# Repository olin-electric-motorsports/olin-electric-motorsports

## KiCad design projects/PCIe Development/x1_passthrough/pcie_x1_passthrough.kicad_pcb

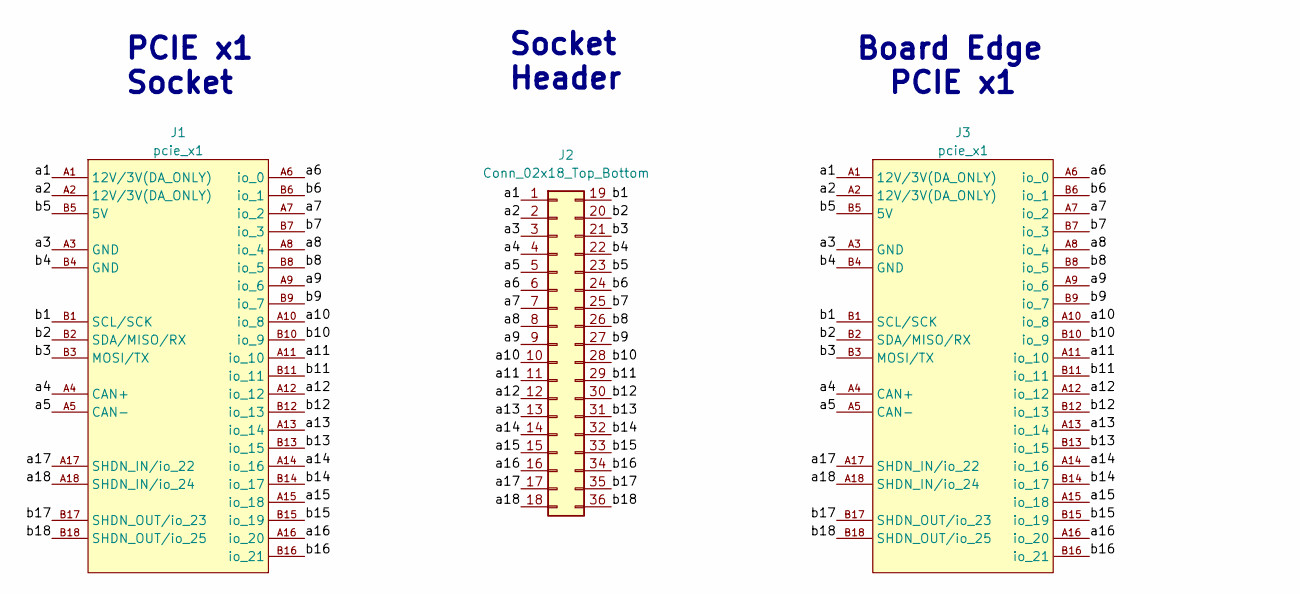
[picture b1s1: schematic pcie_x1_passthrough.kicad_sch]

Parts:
J1: pcie_x1; te_pcie_x1_connector
J2: Conn_02x18_Top_Bottom; PinSocket_2x18_P2.54mm_Vertical
J3: pcie_x1

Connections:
/a1: J1.A1 (12V/3V(DA_ONLY)), J2.1, J3.A1 (12V/3V(DA_ONLY))
/a2: J1.A2 (12V/3V(DA_ONLY)), J2.2, J3.A2 (12V/3V(DA_ONLY))
/a3: J1.A3 (GND), J2.3, J3.A3 (GND)
/a4: J1.A4 (CAN+), J2.4, J3.A4 (CAN+)
/a5: J1.A5 (CAN-), J2.5, J3.A5 (CAN-)
/a6: J1.A6 (io_0), J2.6, J3.A6 (io_0)
/a7: J1.A7 (io_2), J2.7, J3.A7 (io_2)
/a8: J1.A8 (io_4), J2.8, J3.A8 (io_4)
/a9: J1.A9 (io_6), J2.9, J3.A9 (io_6)
/a10: J1.A10 (io_8), J2.10, J3.A10 (io_8)
/a11: J1.A11 (io_10), J2.11, J3.A11 (io_10)
/a12: J1.A12 (io_12), J2.12, J3.A12 (io_12)
/a13: J1.A13 (io_14), J2.13, J3.A13 (io_14)
/a14: J1.A14 (io_16), J2.14, J3.A14 (io_16)
/a15: J1.A15 (io_18), J2.15, J3.A15 (io_18)
/a16: J1.A16 (io_20), J2.16, J3.A16 (io_20)
/a17: J1.A17 (SHDN_IN/io_22), J2.17, J3.A17 (SHDN_IN/io_22)
/a18: J1.A18 (SHDN_IN/io_24), J2.18, J3.A18 (SHDN_IN/io_24)
/b1: J1.B1 (SCL/SCK), J2.19, J3.B1 (SCL/SCK)
/b2: J1.B2 (SDA/MISO/RX), J2.20, J3.B2 (SDA/MISO/RX)
/b3: J1.B3 (MOSI/TX), J2.21, J3.B3 (MOSI/TX)
/b4: J1.B4 (GND), J2.22, J3.B4 (GND)
/b5: J1.B5 (5V), J2.23, J3.B5 (5V)
/b6: J1.B6 (io_1), J2.24, J3.B6 (io_1)
/b7: J1.B7 (io_3), J2.25, J3.B7 (io_3)
/b8: J1.B8 (io_5), J2.26, J3.B8 (io_5)
/b9: J1.B9 (io_7), J2.27, J3.B9 (io_7)
/b10: J1.B10 (io_9), J2.28, J3.B10 (io_9)
/b11: J1.B11 (io_11), J2.29, J3.B11 (io_11)
/b12: J1.B12 (io_13), J2.30, J3.B12 (io_13)
/b13: J1.B13 (io_15), J2.31, J3.B13 (io_15)
/b14: J1.B14 (io_17), J2.32, J3.B14 (io_17)
/b15: J1.B15 (io_19), J2.33, J3.B15 (io_19)
/b16: J1.B16 (io_21), J2.34, J3.B16 (io_21)
/b17: J1.B17 (SHDN_OUT/io_23), J2.35, J3.B17 (SHDN_OUT/io_23)
/b18: J1.B18 (SHDN_OUT/io_25), J2.36, J3.B18 (SHDN_OUT/io_25)

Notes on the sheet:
Socket Header
Board Edge PCIE x1
PCIE x1 Socket

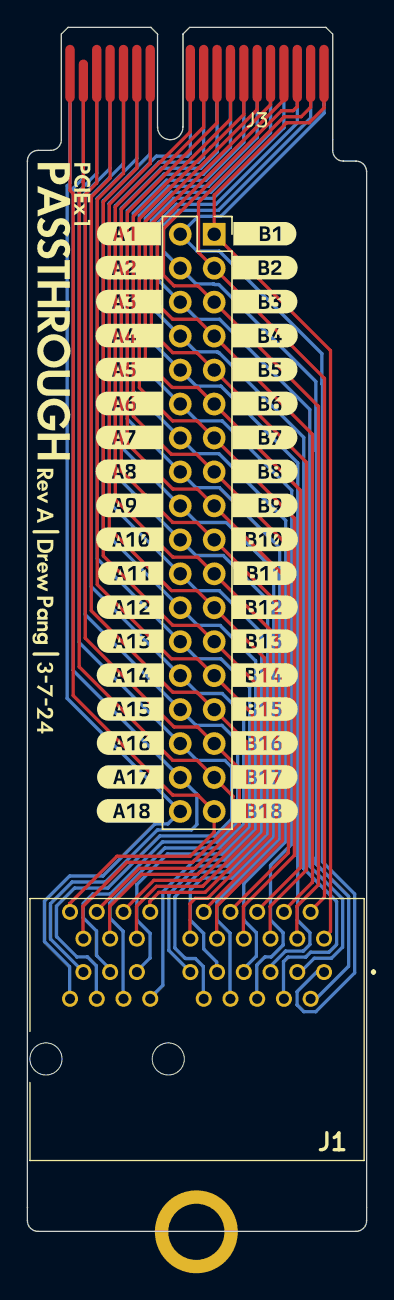
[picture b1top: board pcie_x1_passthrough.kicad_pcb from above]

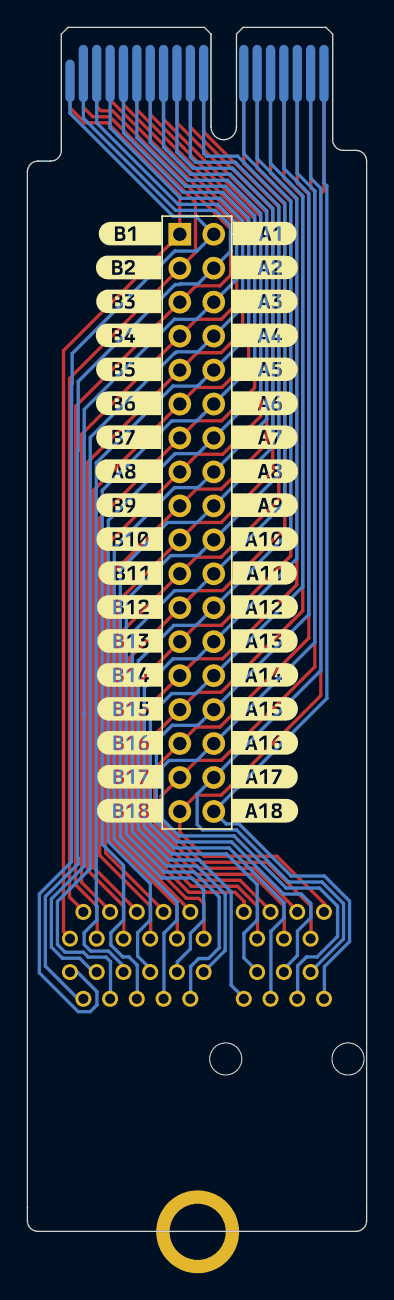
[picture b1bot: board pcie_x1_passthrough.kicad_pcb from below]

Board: 2 copper layers, 25.4 x 90.1 mm, 79 parts (37 on the bottom side), 36 nets.

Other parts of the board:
J2#2: Conn_02x18_Top_Bottom; PinSocket_2x18_P2.54mm_Vertical
kibuzzard-65E95D19: G***; kibuzzard-65E95D19
kibuzzard-65E95DA8: G***; kibuzzard-65E95DA8
kibuzzard-65E95DDF, kibuzzard-65E95DDF#2: G***; kibuzzard-65E95DDF
kibuzzard-65E95DE4: G***; kibuzzard-65E95DE4
kibuzzard-65E95DEB: G***; kibuzzard-65E95DEB
kibuzzard-65E95DEF: G***; kibuzzard-65E95DEF
kibuzzard-65E95DF3: G***; kibuzzard-65E95DF3
kibuzzard-65E95DF8: G***; kibuzzard-65E95DF8
kibuzzard-65E95DFB: G***; kibuzzard-65E95DFB
kibuzzard-65E95E04: G***; kibuzzard-65E95E04
kibuzzard-65E95E8F: G***; kibuzzard-65E95E8F
kibuzzard-65E95E9B: G***; kibuzzard-65E95E9B
kibuzzard-65E95E9E: G***; kibuzzard-65E95E9E
kibuzzard-65E95E93: G***; kibuzzard-65E95E93
kibuzzard-65E95E97: G***; kibuzzard-65E95E97
kibuzzard-65E95EA2: G***; kibuzzard-65E95EA2
kibuzzard-65E95EA8: G***; kibuzzard-65E95EA8
kibuzzard-65E95EAD: G***; kibuzzard-65E95EAD
kibuzzard-65E95F03: G***; kibuzzard-65E95F03
kibuzzard-65E960EE: G***; kibuzzard-65E960EE
kibuzzard-65E962FB: G***; kibuzzard-65E962FB
kibuzzard-65E962FE: G***; kibuzzard-65E962FE
kibuzzard-65E963A3: G***; kibuzzard-65E963A3
kibuzzard-65E963A9: G***; kibuzzard-65E963A9
kibuzzard-65E963AE: G***; kibuzzard-65E963AE
kibuzzard-65E969A0: G***; kibuzzard-65E969A0
kibuzzard-65E969A4: G***; kibuzzard-65E969A4
kibuzzard-65E969AA: G***; kibuzzard-65E969AA
kibuzzard-65E969AE: G***; kibuzzard-65E969AE
kibuzzard-65E969B1: G***; kibuzzard-65E969B1
kibuzzard-65E969B6: G***; kibuzzard-65E969B6
kibuzzard-65E969BA: G***; kibuzzard-65E969BA
kibuzzard-65E969BF: G***; kibuzzard-65E969BF
kibuzzard-65E969C2: G***; kibuzzard-65E969C2
kibuzzard-65E969C6: G***; kibuzzard-65E969C6
kibuzzard-65E969CA: G***; kibuzzard-65E969CA
kibuzzard-65E969CE: G***; kibuzzard-65E969CE
kibuzzard-65E969D2: G***; kibuzzard-65E969D2
kibuzzard-65E969D5: G***; kibuzzard-65E969D5
kibuzzard-65E969DA: G***; kibuzzard-65E969DA
kibuzzard-65E969DD: G***; kibuzzard-65E969DD
kibuzzard-65E969E1: G***; kibuzzard-65E969E1
kibuzzard-65E969E5: G***; kibuzzard-65E969E5
kibuzzard-65E969E9: G***; kibuzzard-65E969E9
kibuzzard-65E969ED: G***; kibuzzard-65E969ED
kibuzzard-65E9630A: G***; kibuzzard-65E9630A
kibuzzard-65E9633C: G***; kibuzzard-65E9633C
kibuzzard-65E9636C: G***; kibuzzard-65E9636C
kibuzzard-65E9638D: G***; kibuzzard-65E9638D
kibuzzard-65E9639B: G***; kibuzzard-65E9639B
kibuzzard-65E9639F: G***; kibuzzard-65E9639F
kibuzzard-65E9696D: G***; kibuzzard-65E9696D
kibuzzard-65E9697B: G***; kibuzzard-65E9697B
kibuzzard-65E9698D: G***; kibuzzard-65E9698D
kibuzzard-65E9699C: G***; kibuzzard-65E9699C
kibuzzard-65E96100: G***; kibuzzard-65E96100
kibuzzard-65E96303: G***; kibuzzard-65E96303
kibuzzard-65E96310: G***; kibuzzard-65E96310
kibuzzard-65E96314: G***; kibuzzard-65E96314
kibuzzard-65E96318: G***; kibuzzard-65E96318
kibuzzard-65E96322: G***; kibuzzard-65E96322
kibuzzard-65E96383: G***; kibuzzard-65E96383
kibuzzard-65E96396: G***; kibuzzard-65E96396
kibuzzard-65E96959: G***; kibuzzard-65E96959
kibuzzard-65E96962: G***; kibuzzard-65E96962
kibuzzard-65E96967: G***; kibuzzard-65E96967
kibuzzard-65E96973: G***; kibuzzard-65E96973
kibuzzard-65E96977: G***; kibuzzard-65E96977
kibuzzard-65E96980: G***; kibuzzard-65E96980
kibuzzard-65E96984: G***; kibuzzard-65E96984
kibuzzard-65E96989: G***; kibuzzard-65E96989
kibuzzard-65E96991: G***; kibuzzard-65E96991
kibuzzard-65E96995: G***; kibuzzard-65E96995
kibuzzard-65E96999: G***; kibuzzard-65E96999

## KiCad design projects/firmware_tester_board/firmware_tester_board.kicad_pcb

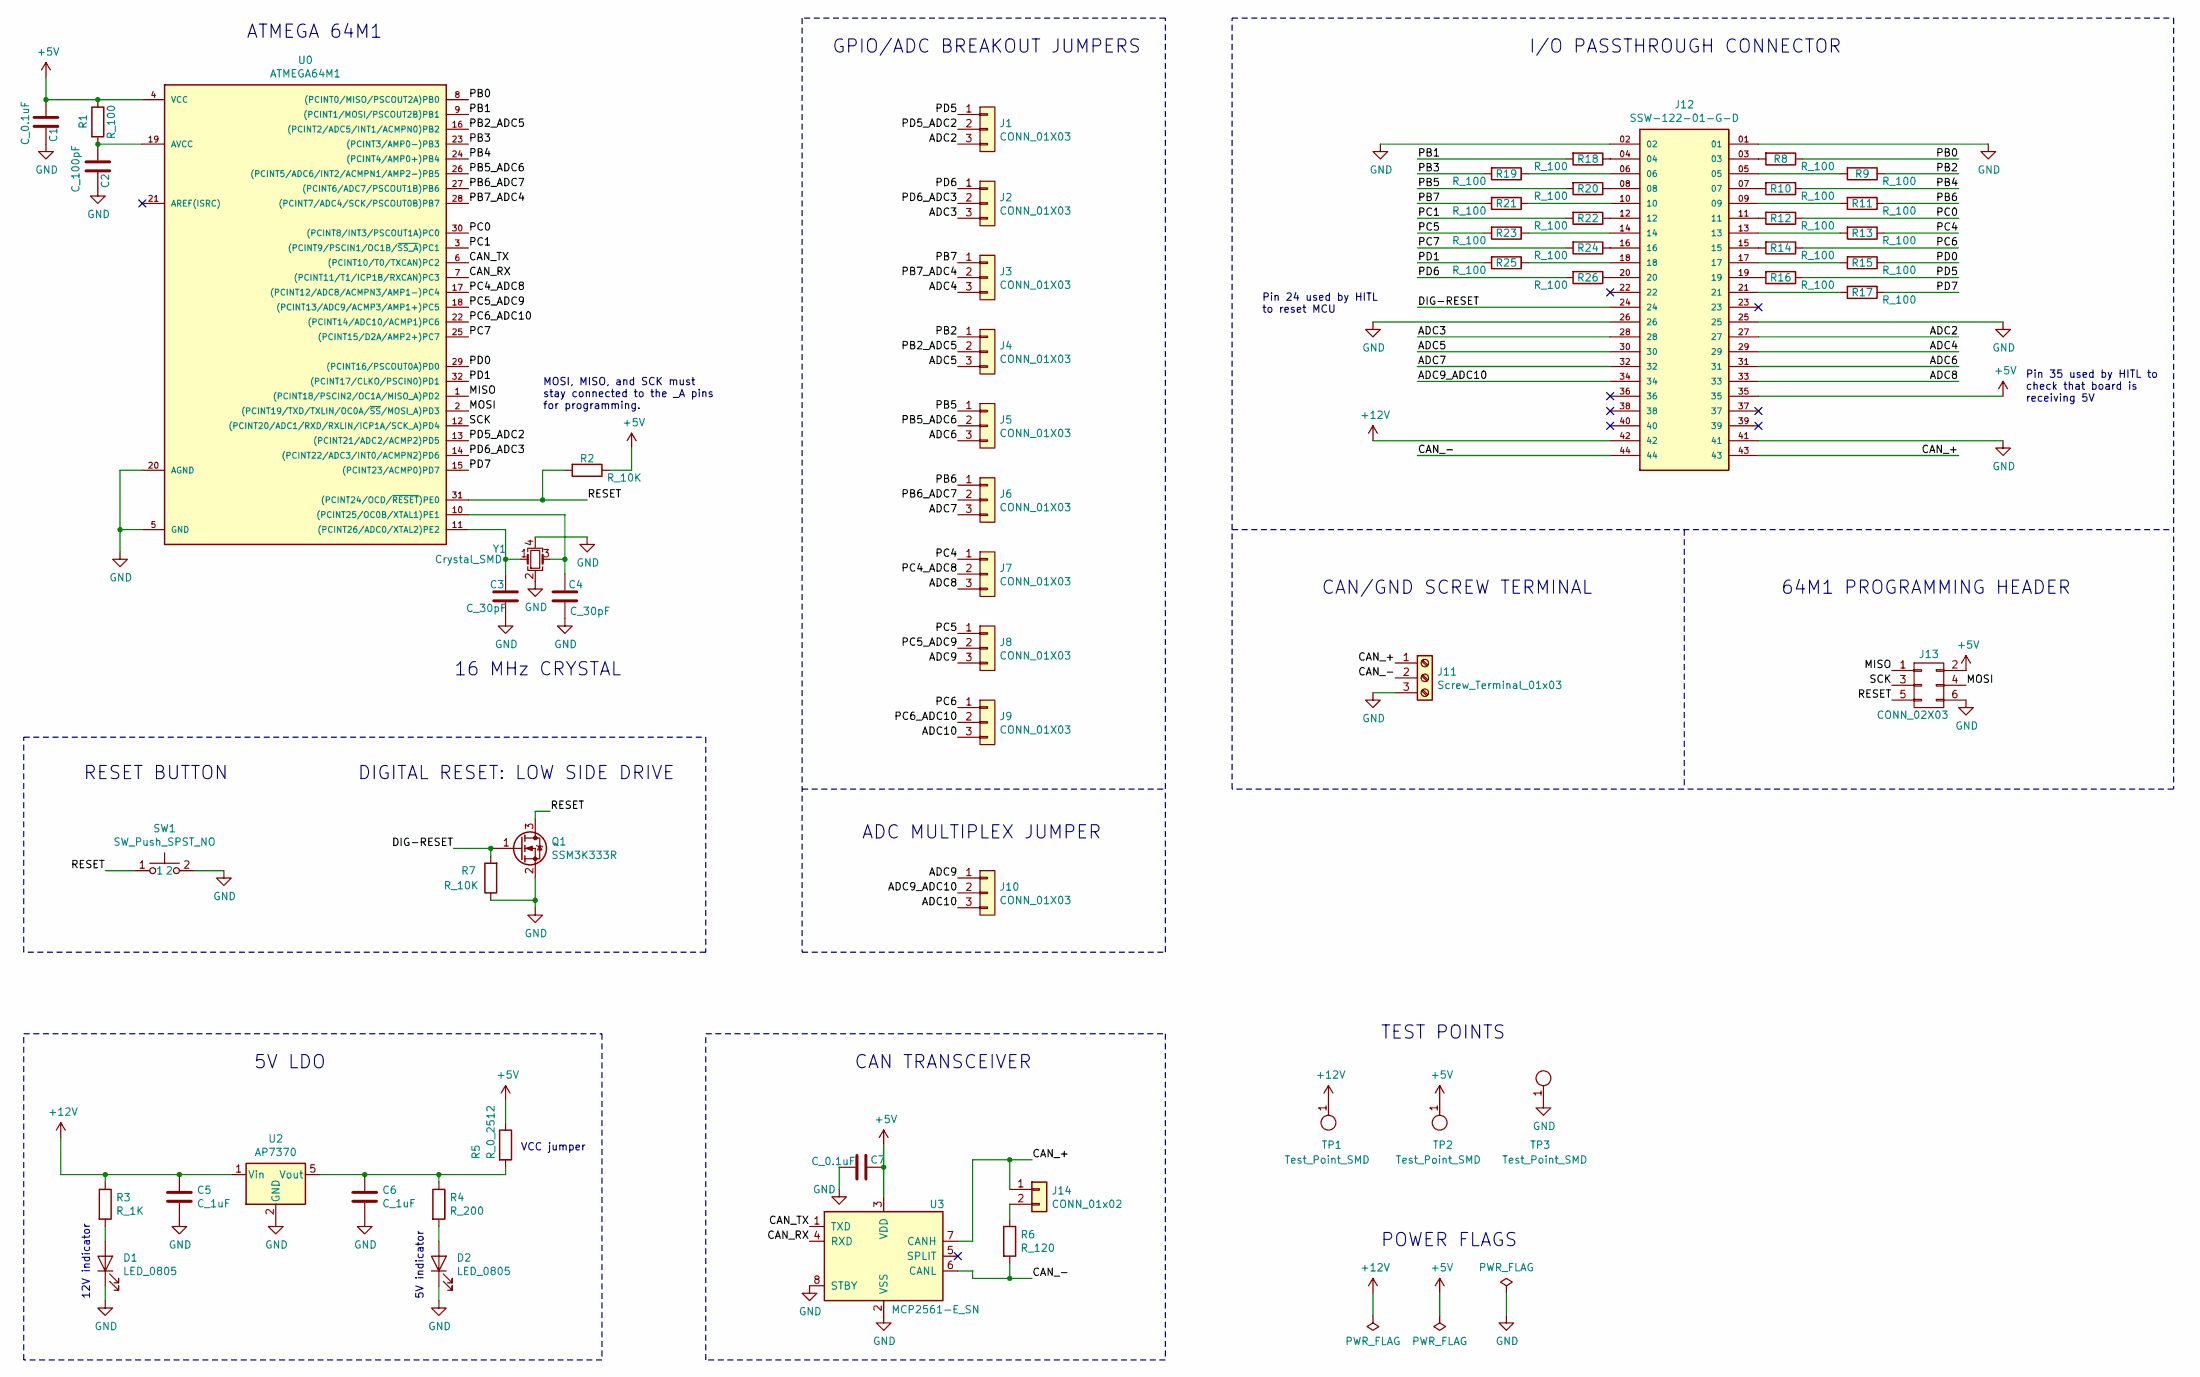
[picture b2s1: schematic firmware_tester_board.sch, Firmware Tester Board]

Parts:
C1, C7: C_0.1uF; C_0805_OEM; MPN 478-3352-1-ND
C2: C_100pF; C_0805_OEM; MPN 732-7852-1-ND
C3, C4: C_30pF; C_0805_OEM; MPN 1276-1130-1-ND
C5, C6: C_1uF; C_0805_OEM
D1, D2: LED_0805; LED_0805_OEM; MPN 475-1410-1-ND
J1, J2, J3, J4, J5, J6, J7, J8, J9, J10: CONN_01X03; PinHeader_1x03_P2.54mm_Vertical; MPN 855-M20-9990346
J11: Screw_Terminal_01x03; TerminalBlock_Phoenix_MKDS-1,5-3_1x03_P5.00mm_Horizontal
J12: SSW-122-01-G-D; SAMTEC_SSW-122-01-G-D; MPN 61304421121
J13: CONN_02X03; Pin_Header_Straight_2x03; MPN 609-3234-ND
J14: CONN_01x02; PinSocket_1x02_P2.54mm_Vertical; MPN 732-5315-ND
Q1: SSM3K333R; SOT-23F; MPN SSM3K333RLFCT-ND
R1, R8, R9, R10, R11, R12, R13, R14, R15, R16, R17, R18, R19, R20, R21, R22, R23, R24, R25, R26: R_100; R_0805_OEM; MPN RNCP0805FTD100RCT-ND
R2, R7: R_10K; R_0805_OEM; MPN CRS0805-FX-1002ELFCT-ND
R3: R_1K; R_0805_OEM; MPN RNCP0805FTD1K00CT-ND
R4: R_200; R_0805_OEM; MPN RMCF0805JT200RCT-ND
R5: R_0_2512; R_2512_OEM; MPN A121322CT-ND
R6: R_120; R_0805_OEM; MPN 667-ERJ-6ENF1200V
SW1: SW_Push_SPST_NO; SW_B3U-1000P_4.2x1.7mm; MPN SW1020CT-ND
TP1, TP2, TP3: Test_Point_SMD
U0: ATMEGA64M1; TQFP-32_7x7mm_Pitch0.8mm; MPN ATMEGA16M1-AU-ND
U2: AP7370; SOT-23-5; MPN AP7370-50W5-7DICT-ND
U3: MCP2561-E_SN; SOIC-8_3.9x4.9mm_Pitch1.27mm_OEM; MPN MCP2561-E/SN-ND
Y1: Crystal_SMD; Crystal_SMD_FA238; MPN 887-1125-1-ND

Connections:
+5V: C1.1, C7.1, J12.35, J13.2, R1.1, R2.1, R5.1, TP2.1, U0.4 (VCC), U3.3 (VDD)
+12V: C5.1, J12.42, R3.1, TP1.1, U2.1 (Vin)
/ADC2: J1.3, J12.27
/ADC3: J2.3, J12.28
/ADC4: J3.3, J12.29
/ADC5: J4.3, J12.30
/ADC6: J5.3, J12.31
/ADC7: J6.3, J12.32
/ADC8: J7.3, J12.33
/ADC9: J8.3, J10.1
/ADC9_ADC10: J10.2, J12.34
/ADC10: J9.3, J10.3
/CAN_+: J11.1, J12.43, J14.1, U3.7 (CANH)
/CAN_-: J11.2, J12.44, R6.2, U3.6 (CANL)
/CAN_RX: U0.7 ((PCINT11/T1/ICP1B/RXCAN)PC3), U3.4 (RXD)
/CAN_TX: U0.6 ((PCINT10/T0/TXCAN)PC2), U3.1 (TXD)
/DIG-RESET: J12.24, Q1.1 (G), R7.2
/MISO: J13.1, U0.1 ((PCINT18/PSCIN2/OC1A/MISO_A)PD2)
/MOSI: J13.4, U0.2 ((PCINT19/TXD/TXLIN/OC0A/~SS~/MOSI_A)PD3)
/PB0: R8.1, U0.8 ((PCINT0/MISO/PSCOUT2A)PB0)
/PB1: R18.2, U0.9 ((PCINT1/MOSI/PSCOUT2B)PB1)
/PB2: J4.1, R9.1
/PB2_ADC5: J4.2, U0.16 ((PCINT2/ADC5/INT1/ACMPN0)PB2)
/PB3: R19.2, U0.23 ((PCINT3/AMP0-)PB3)
/PB4: R10.1, U0.24 ((PCINT4/AMP0+)PB4)
/PB5: J5.1, R20.2
/PB5_ADC6: J5.2, U0.26 ((PCINT5/ADC6/INT2/ACMPN1/AMP2-)PB5)
/PB6: J6.1, R11.1
/PB6_ADC7: J6.2, U0.27 ((PCINT6/ADC7/PSCOUT1B)PB6)
/PB7: J3.1, R21.2
/PB7_ADC4: J3.2, U0.28 ((PCINT7/ADC4/SCK/PSCOUT0B)PB7)
/PC0: R12.1, U0.30 ((PCINT8/INT3/PSCOUT1A)PC0)
/PC1: R22.2, U0.3 ((PCINT9/PSCIN1/OC1B/~SS_A~)PC1)
/PC4: J7.1, R13.1
/PC4_ADC8: J7.2, U0.17 ((PCINT12/ADC8/ACMPN3/AMP1-)PC4)
/PC5: J8.1, R23.2
/PC5_ADC9: J8.2, U0.18 ((PCINT13/ADC9/ACMP3/AMP1+)PC5)
/PC6: J9.1, R14.1
/PC6_ADC10: J9.2, U0.22 ((PCINT14/ADC10/ACMP1)PC6)
/PC7: R24.2, U0.25 ((PCINT15/D2A/AMP2+)PC7)
/PD0: R15.1, U0.29 ((PCINT16/PSCOUT0A)PD0)
/PD1: R25.2, U0.32 ((PCINT17/CLKO/PSCIN0)PD1)
/PD5: J1.1, R16.1
/PD5_ADC2: J1.2, U0.13 ((PCINT21/ADC2/ACMP2)PD5)
/PD6: J2.1, R26.2
/PD6_ADC3: J2.2, U0.14 ((PCINT22/ADC3/INT0/ACMPN2)PD6)
/PD7: R17.1, U0.15 ((PCINT23/ACMP0)PD7)
/RESET: J13.5, Q1.3 (D), R2.2, SW1.1, U0.31 ((PCINT24/OCD/~RESET~)PE0)
/SCK: J13.3, U0.12 ((PCINT20/ADC1/RXD/RXLIN/ICP1A/SCK_A)PD4)
GND: C1.2, C2.2, C3.2, C4.2, C5.2, C6.2, C7.2, D1.1 (K), D2.1 (K), J11.3, J12.01, J12.02, J12.25, J12.26, J12.41, J13.6, Q1.2 (S), R7.1, SW1.2, TP3.1, U0.5 (GND), U0.20 (AGND), U2.2 (GND), U3.2 (VSS), U3.8 (STBY), Y1.2, Y1.4
unnamed: C2.1, R1.2, U0.19 (AVCC)
unnamed: C3.1, U0.11 ((PCINT26/ADC0/XTAL2)PE2), Y1.1
unnamed: C4.1, U0.10 ((PCINT25/OC0B/XTAL1)PE1), Y1.3
unnamed: C6.1, R4.1, R5.2, U2.5 (Vout)
unnamed: D1.2 (A), R3.2
unnamed: D2.2 (A), R4.2
unnamed: J12.03, R8.2
unnamed: J12.04, R18.1
unnamed: J12.05, R9.2
unnamed: J12.06, R19.1
unnamed: J12.07, R10.2
unnamed: J12.08, R20.1
unnamed: J12.09, R11.2
unnamed: J12.10, R21.1
unnamed: J12.11, R12.2
unnamed: J12.12, R22.1
unnamed: J12.13, R13.2
unnamed: J12.14, R23.1
unnamed: J12.15, R14.2
unnamed: J12.16, R24.1
unnamed: J12.17, R15.2
unnamed: J12.18, R25.1
unnamed: J12.19, R16.2
unnamed: J12.20, R26.1
unnamed: J12.21, R17.2
unnamed: J14.2, R6.1

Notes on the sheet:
CAN TRANSCEIVER
ATMEGA 64M1
16 MHz CRYSTAL
64M1 PROGRAMMING HEADER
MOSI, MISO, and SCK must stay connected to the _A pins for programming.
GPIO/ADC BREAKOUT JUMPERS
I/O PASSTHROUGH CONNECTOR
CAN/GND SCREW TERMINAL
RESET BUTTON
5V LDO
ADC MULTIPLEX JUMPER
DIGITAL RESET: LOW SIDE DRIVE
12V indicator
5V indicator
VCC jumper
TEST POINTS
Pin 35 used by HITL to check that board is receiving 5V
POWER FLAGS
Pin 24 used by HITL to reset MCU

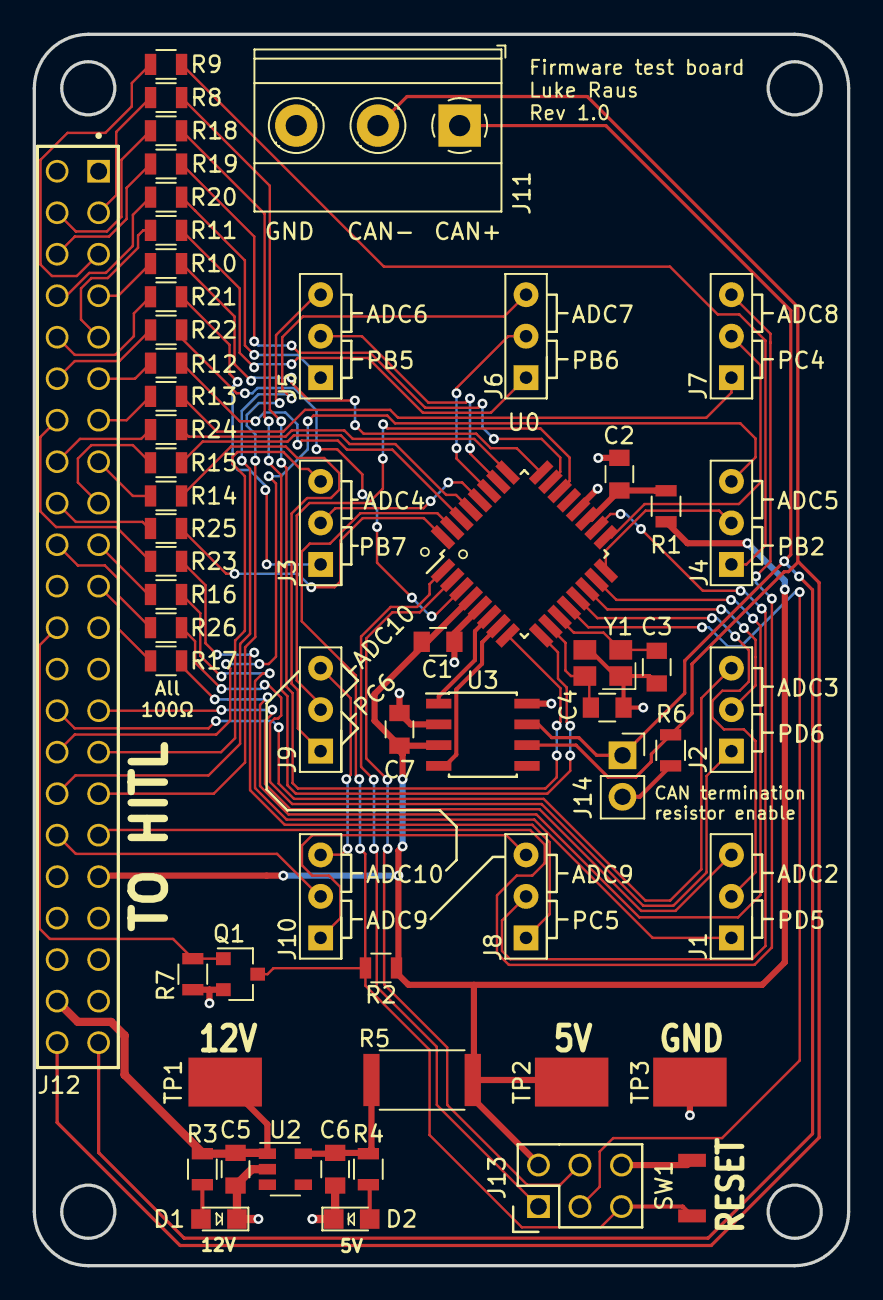
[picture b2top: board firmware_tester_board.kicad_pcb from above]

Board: 2 copper layers, 49.8 x 75.4 mm, 58 parts (0 on the bottom side), 76 nets.

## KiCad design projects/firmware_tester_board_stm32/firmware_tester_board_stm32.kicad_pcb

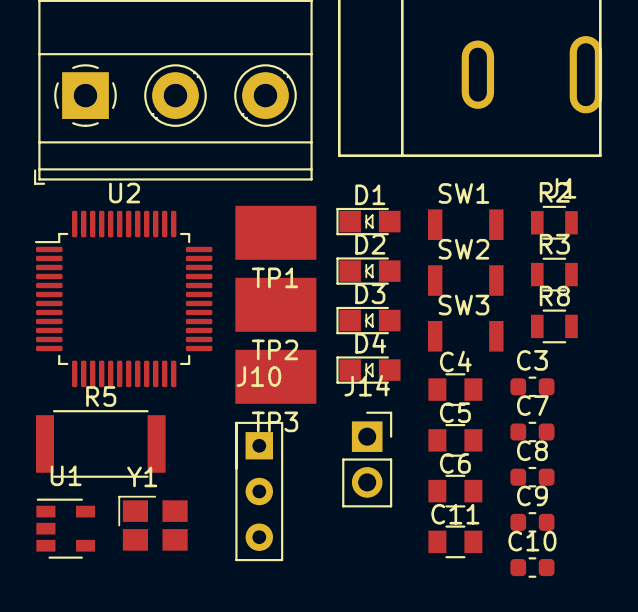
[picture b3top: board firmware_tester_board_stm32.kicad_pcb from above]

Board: 2 copper layers, 30 parts (0 on the bottom side), 12 nets, no tracks yet.

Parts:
C3, C7, C8, C9, C10: C_100nF; C_0603_1608Metric
C4, C5, C6: C_1uF; C_0805_OEM
C11: C_0.1uF; C_0805_OEM
D1, D2, D3: LED_0805; LED_0805_OEM
D4: LED_0805_Amber; LED_0805_OEM
J1: Barrel_jack; barrel_jack_PJ-037A
J10: CONN_01X03; PinHeader_1x03_P2.54mm_Vertical
J12: Screw_Terminal_01x03; TerminalBlock_Phoenix_MKDS-1,5-3_1x03_P5.00mm_Horizontal
J14: CONN_01x02; PinSocket_1x02_P2.54mm_Vertical
R2: R_1K; R_0805_OEM
R3: R_200; R_0805_OEM
R5: R_0_2512; R_2512_OEM
R8: R_120; R_0805_OEM
SW1, SW2, SW3: SW_Push_SPST_NO; SW_B3U-1000P_4.2x1.7mm
TP1, TP2, TP3: Test_Point_SMD
U1: AP7370; SOT-23-5
U2: STM32F103C8Tx; LQFP-48_7x7mm_P0.5mm
Y1: Crystal_SMD; Crystal_SMD_FA238

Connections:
+3V3: C3.1, C6.1, C7.1, C8.1, C9.1, C10.1, SW2.1, SW3.1, U2.1 (VBAT), U2.9 (VDDA), U2.24 (VDD), U2.36 (VDD), U2.48 (VDD)
+5V: R5.1, TP2.1
+12V: C4.1, J1.1 (center), R2.1, TP1.1, U1.1 (Vin)
/CAN1_+: J12.1, J14.1
/CAN1_-: J12.2, R8.2
/NRST: SW1.1, U2.7 (NRST)
GND: C3.2, C4.2, C5.2, C6.2, C7.2, C8.2, C9.2, C10.2, C11.2, D1.1 (K), D2.1 (K), D3.1 (K), D4.1 (K), J1.2 (Shell), J12.3, SW1.2, TP3.1, U1.2 (GND), U2.8 (VSSA), U2.23 (VSS), U2.35 (VSS), U2.47 (VSS), Y1.2, Y1.4
unnamed: D1.2 (A), R2.2
unnamed: D2.2 (A), R3.2
unnamed: J14.2, R8.1
unnamed: C5.1, R3.1, R5.2, U1.5 (Vout)
unnamed: U2.5 (PD0), Y1.1

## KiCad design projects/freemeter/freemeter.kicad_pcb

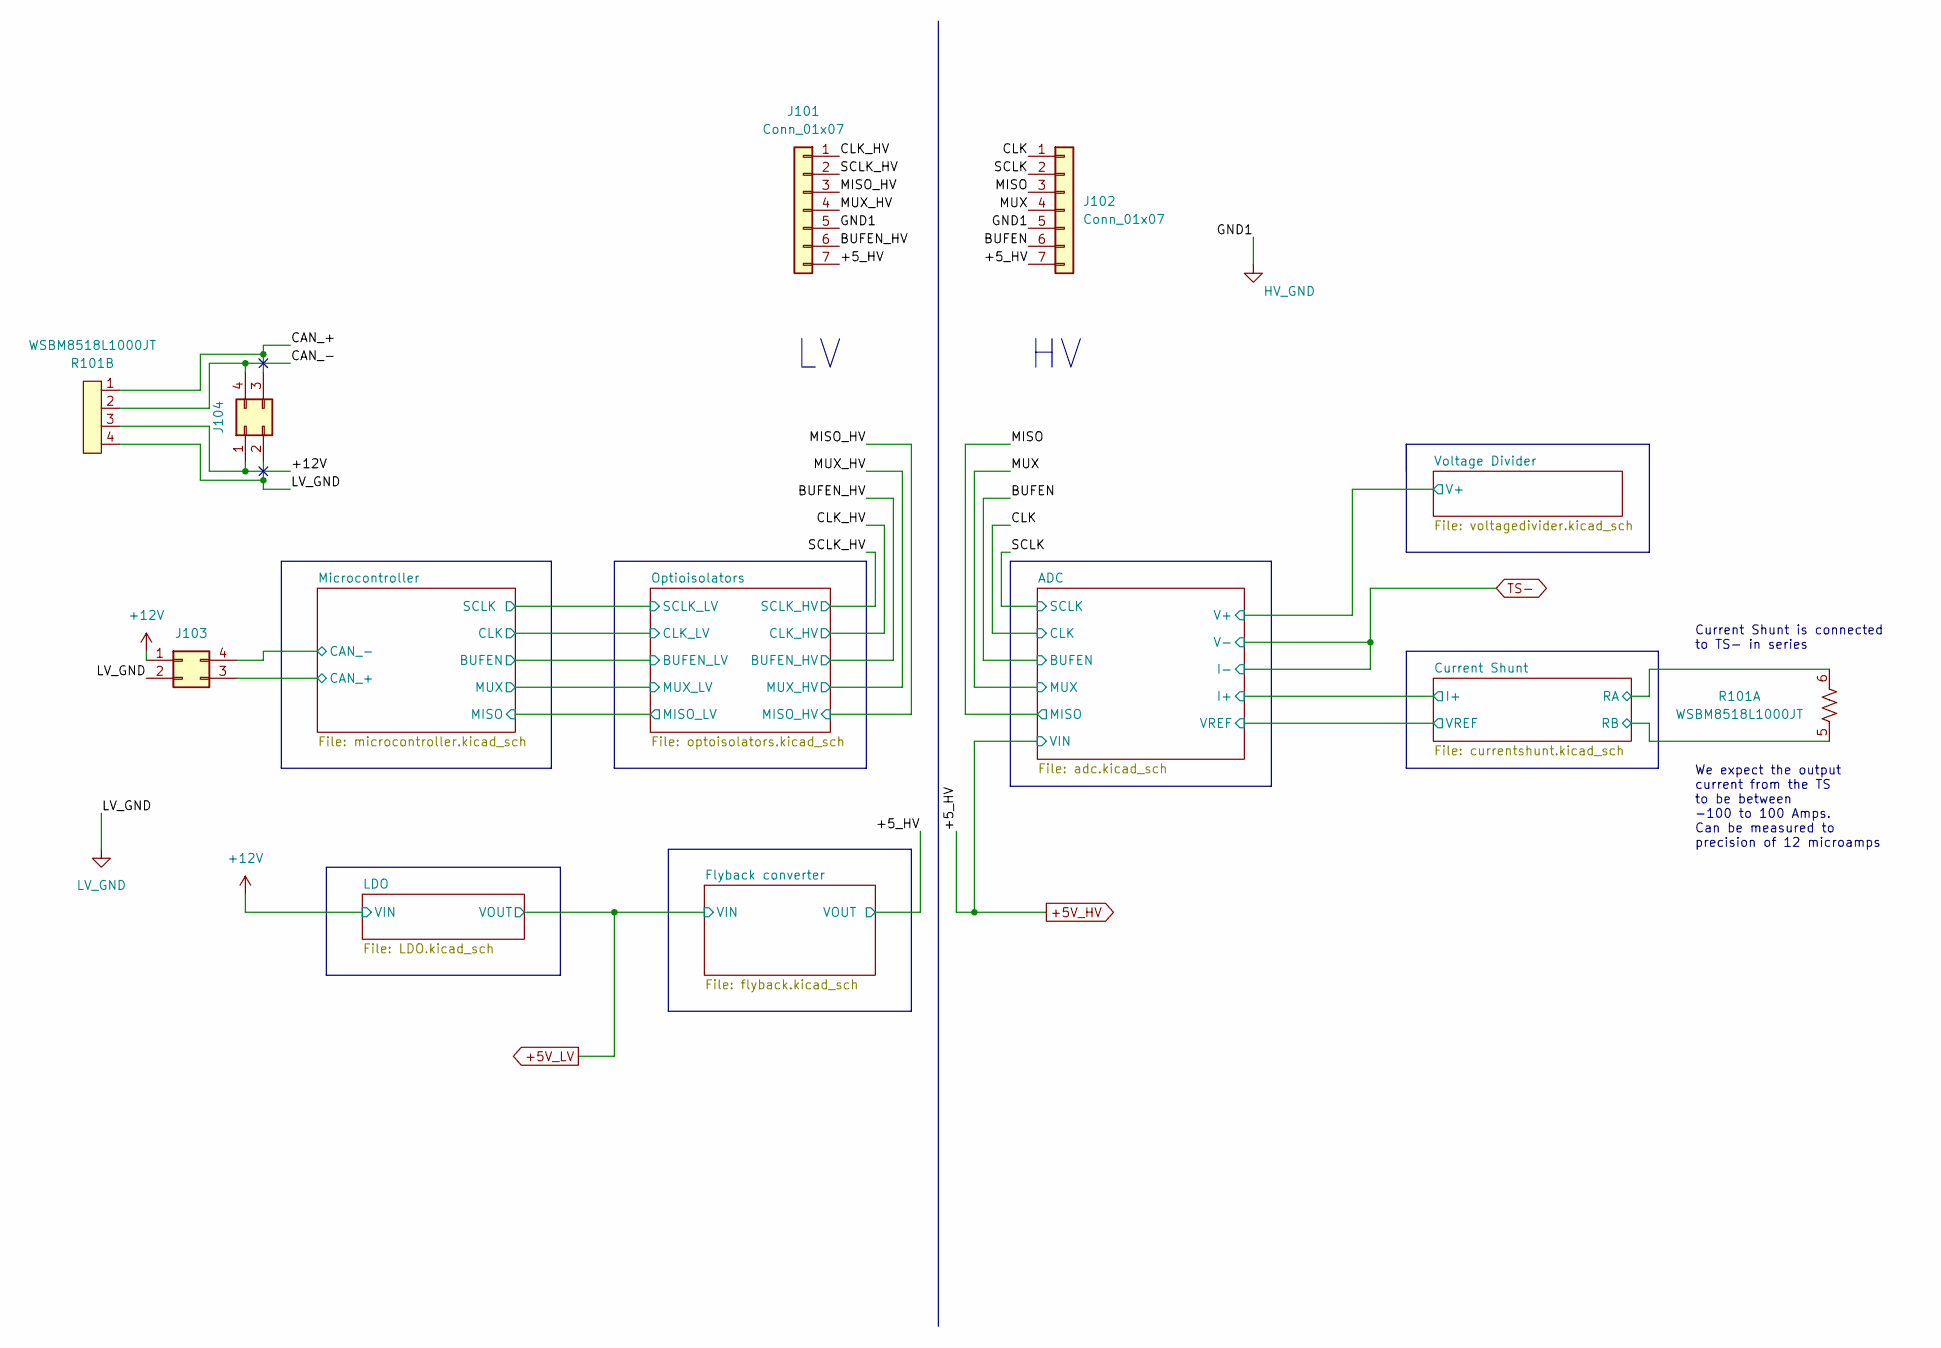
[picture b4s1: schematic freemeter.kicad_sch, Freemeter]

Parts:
J101, J102: Conn_01x07; PinHeader_1x07_P2.54mm_Vertical
J103, J104: Conn_02x02_Counter_Clockwise; PinHeader_2x02_P2.54mm_Vertical
R101: WSBM8518L1000JT; Vishay_WSB

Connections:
+5V_HV: J101.7, J102.7; also elsewhere on the board
+12V: J103.1, J104.1, R101.3; also elsewhere on the board
/BUFEN: J102.6; also elsewhere on the board
/BUFEN_HV: J101.6; also elsewhere on the board
/CAN_+: J104.3, R101.1; also elsewhere on the board
/CAN_-: J104.4, R101.2; also elsewhere on the board
/CLK: J102.1; also elsewhere on the board
/CLK_HV: J101.1; also elsewhere on the board
/MISO: J102.3; also elsewhere on the board
/MISO_HV: J101.3; also elsewhere on the board
/MUX: J102.4; also elsewhere on the board
/MUX_HV: J101.4; also elsewhere on the board
/Microcontroller /CAN_+: J103.3; also elsewhere on the board
/Microcontroller /CAN_-: J103.4; also elsewhere on the board
/SCLK: J102.2; also elsewhere on the board
/SCLK_HV: J101.2; also elsewhere on the board

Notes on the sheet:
Current Shunt is connected to TS- in series
We expect the output current from the TS to be between -100 to 100 Amps. Can be measured to precision of 12 microamps

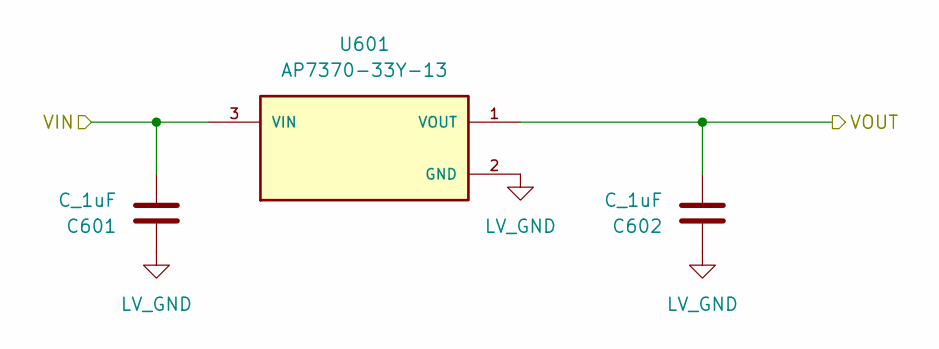
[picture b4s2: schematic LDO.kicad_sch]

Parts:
C601, C602: C_1uF; C_0603_1608Metric; MPN 1276-6470-1-ND
U601: AP7370-33Y-13; PARTREV 1 - 2

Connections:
+5V_LV: C602.1, U601.1 (VOUT); also elsewhere on the board
+12V: C601.1, U601.3 (VIN); also elsewhere on the board

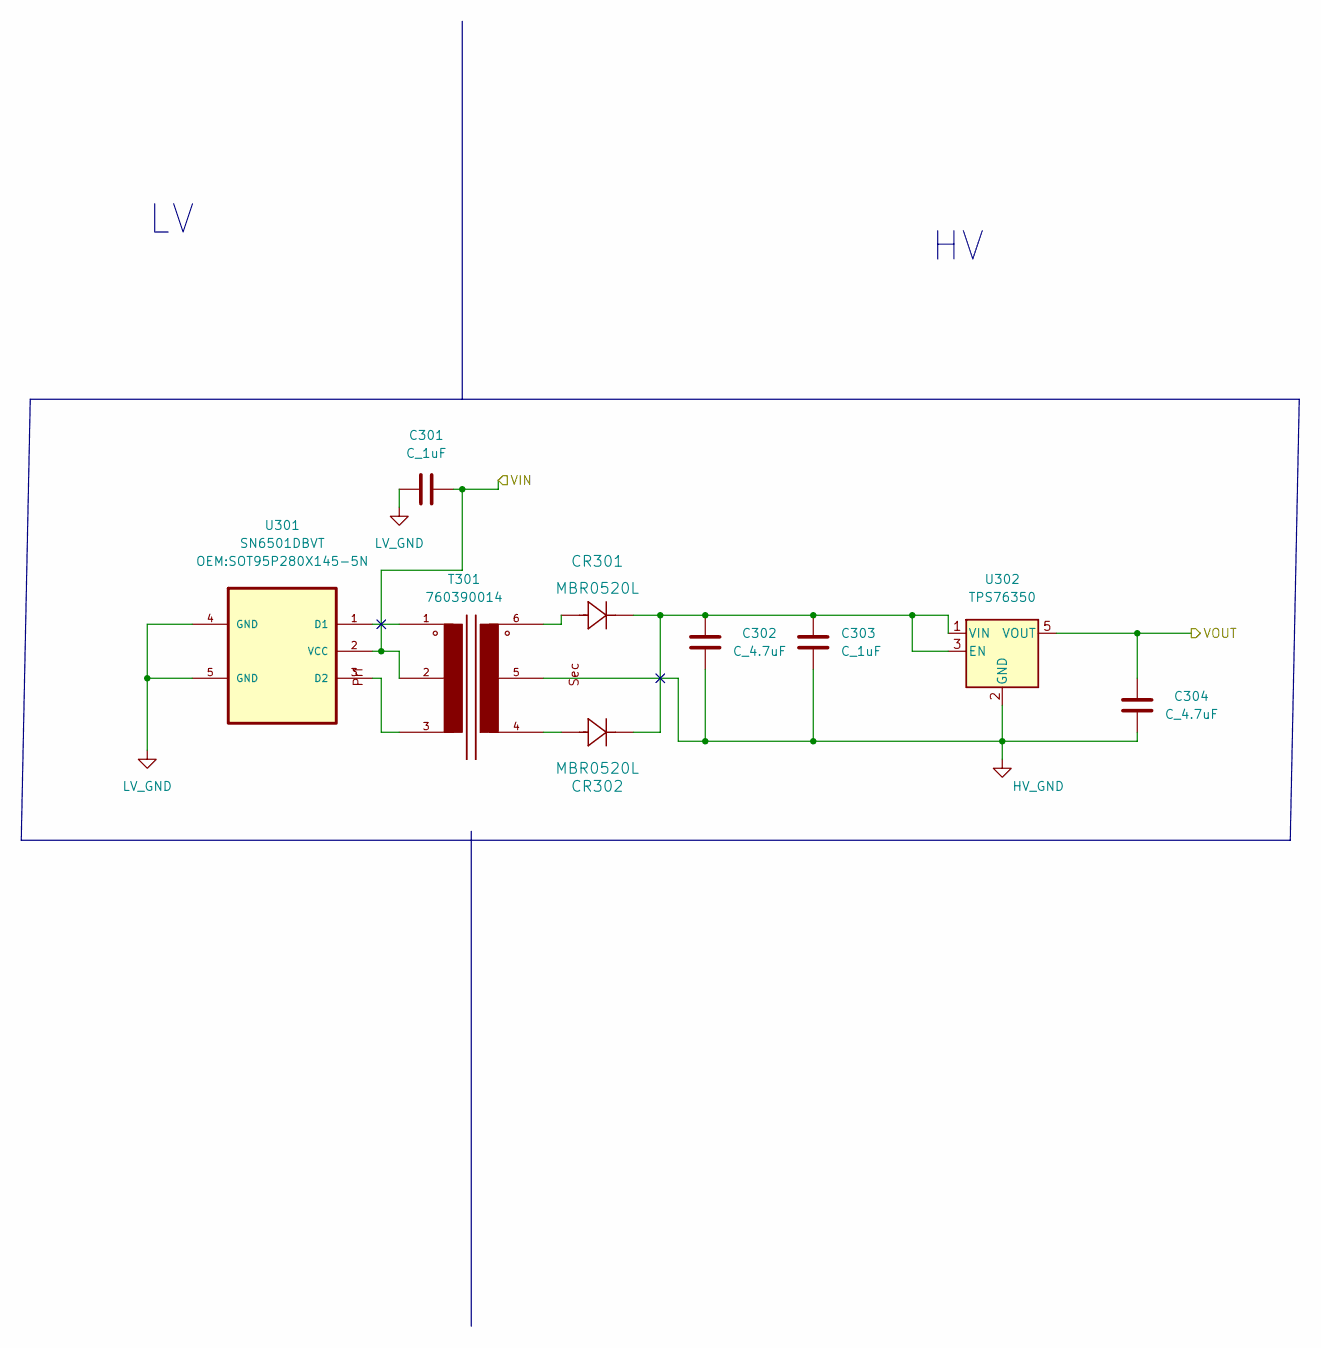
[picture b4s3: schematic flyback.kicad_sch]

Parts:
C301, C303: C_1uF; C_0603_1608Metric; MPN 1276-6470-1-ND
C302, C304: C_4.7uF; C_0603_1608Metric; MPN 1276-1045-1-ND
CR301, CR302: MBR0520L
T301: 760390014
U301: SN6501DBVT; SOT95P280X145-5N
U302: TPS76350; SOT-23-5

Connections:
+5V_HV: C304.1, U302.5 (VOUT); also elsewhere on the board
+5V_LV: C301.2, T301.2, U301.2 (VCC); also elsewhere on the board
unnamed: C302.1, C303.1, CR301.1, CR302.1, U302.1 (VIN), U302.3 (EN)
unnamed: CR301.2, T301.6
unnamed: CR302.2, T301.4
unnamed: T301.1, U301.1 (D1)
unnamed: T301.3, U301.3 (D2)

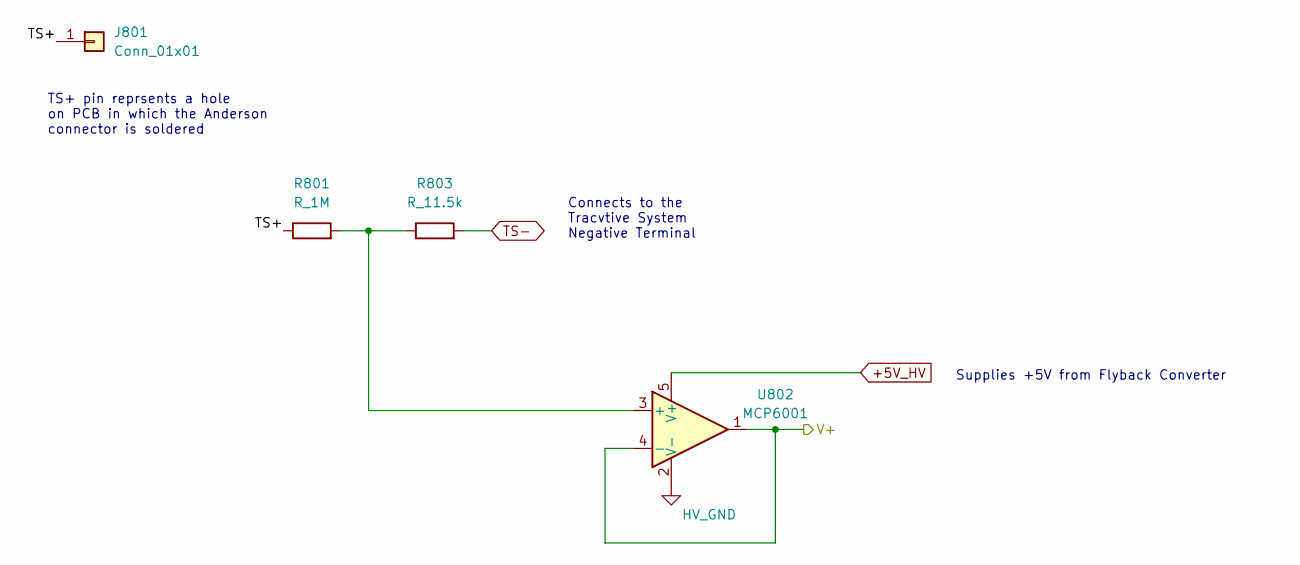
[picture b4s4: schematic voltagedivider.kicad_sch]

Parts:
J801: Conn_01x01; TestPoint_Plated_Hole_D3.0mm
R801: R_1M; R_0603_1608Metric; MPN RMCF0805JT1M00CT-ND
R803: R_11.5k; R_0603_1608Metric
U802: MCP6001; SOT-23-5; MPN MCP6001T

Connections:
+5V_HV: U802.5 (V+); also elsewhere on the board
/ADC/V+: U802.1, U802.4 (-); also elsewhere on the board
/Voltage Divider/TS+: J801.1, R801.1
unnamed: R801.2, R803.1, U802.3 (+)
TS-: R803.2; also elsewhere on the board

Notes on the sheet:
Supplies +5V from Flyback Converter
TS+ pin reprsents a hole on PCB in which the Anderson connector is soldered
Connects to the Tracvtive System Negative Terminal

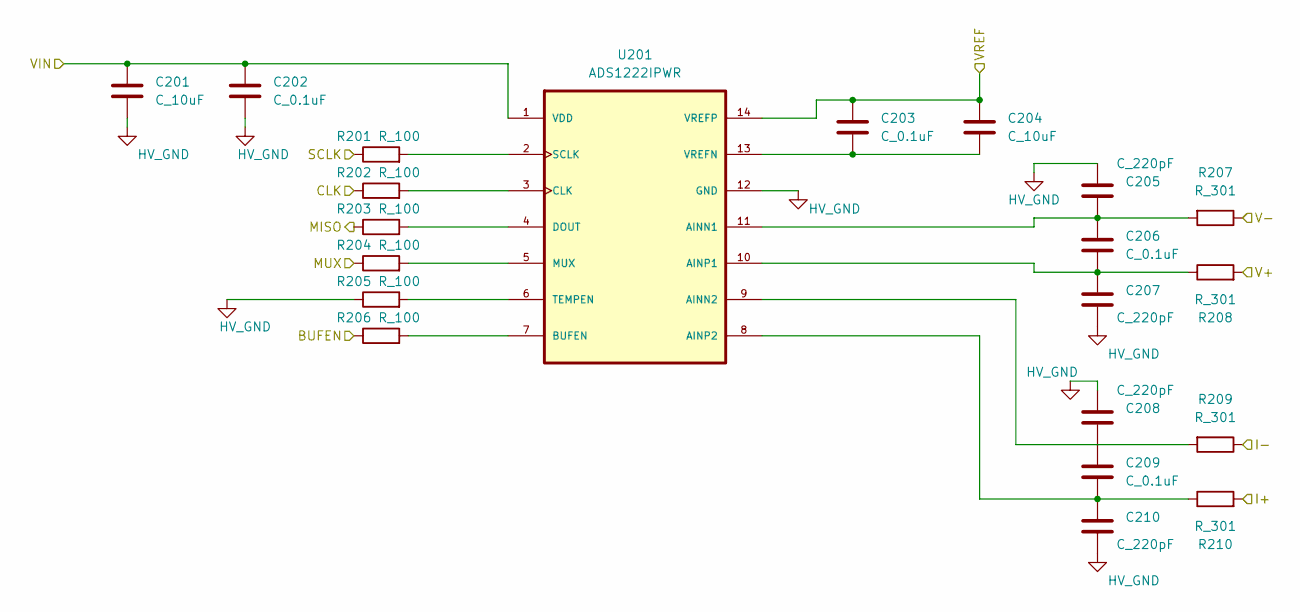
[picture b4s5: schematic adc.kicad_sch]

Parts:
C201, C204: C_10uF; C_0603_1608Metric; MPN 1276-1052-1-ND
C202, C203, C206, C209: C_0.1uF; C_0603_1608Metric; MPN 478-3352-1-ND
C205, C207, C208, C210: C_220pF; C_0603_1608Metric; MPN 478-3352-1-ND
R201, R202, R203, R204, R205, R206: R_100; R_0603_1608Metric; MPN RNCP0805FTD100RCT-ND
R207, R208, R209, R210: R_301; R_0603_1608Metric
U201: ADS1222IPWR

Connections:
+5V_HV: C201.1, C202.1, U201.1 (VDD); also elsewhere on the board
/ADC/I+: R210.2; also elsewhere on the board
/ADC/V+: R208.2; also elsewhere on the board
/ADC/VREF: C203.1, C204.1, U201.14 (VREFP); also elsewhere on the board
/BUFEN: R206.1; also elsewhere on the board
/CLK: R202.1; also elsewhere on the board
/MISO: R203.1; also elsewhere on the board
/MUX: R204.1; also elsewhere on the board
/SCLK: R201.1; also elsewhere on the board
unnamed: C203.2, C204.2, U201.13 (VREFN)
unnamed: C205.2, C206.1, R207.2, U201.11 (AINN1)
unnamed: C206.2, C207.1, R208.1, U201.10 (AINP1)
unnamed: C208.2, C209.1
unnamed: C209.2, C210.1, R210.1, U201.8 (AINP2)
unnamed: R201.2, U201.2 (SCLK)
unnamed: R202.2, U201.3 (CLK)
unnamed: R203.2, U201.4 (DOUT)
unnamed: R204.2, U201.5 (MUX)
unnamed: R205.2, U201.6 (TEMPEN)
unnamed: R206.2, U201.7 (BUFEN)
unnamed: R209.2, U201.9 (AINN2)
TS-: R207.1, R209.1; also elsewhere on the board

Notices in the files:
parts and their libraries:
Copyright 2021 Accelerated Designs. All rights reserved.
